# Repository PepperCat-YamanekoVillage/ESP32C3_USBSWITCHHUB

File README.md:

LICENSE -> https://creativecommons.org/licenses/by-nc-sa/4.0/

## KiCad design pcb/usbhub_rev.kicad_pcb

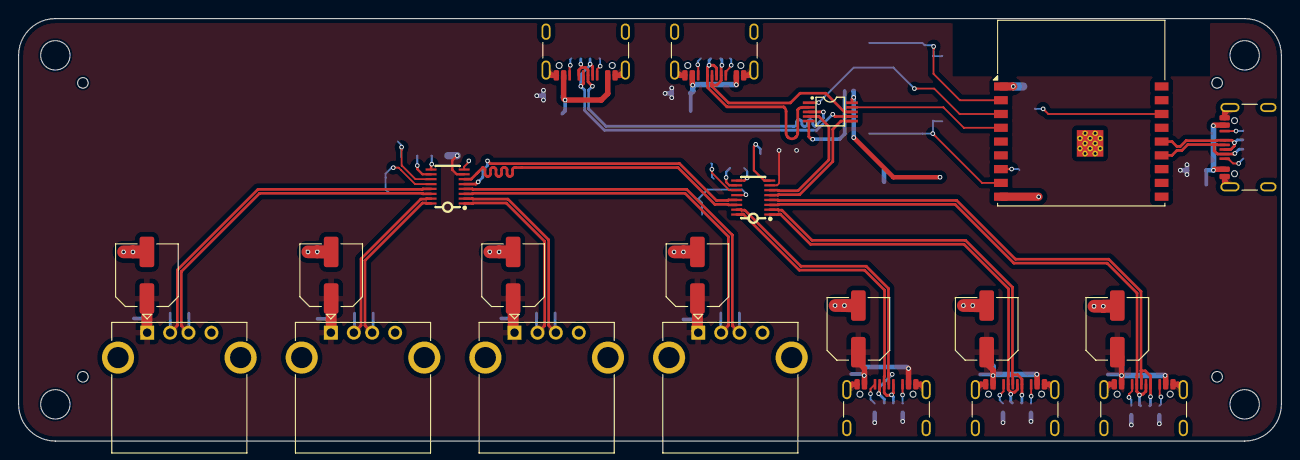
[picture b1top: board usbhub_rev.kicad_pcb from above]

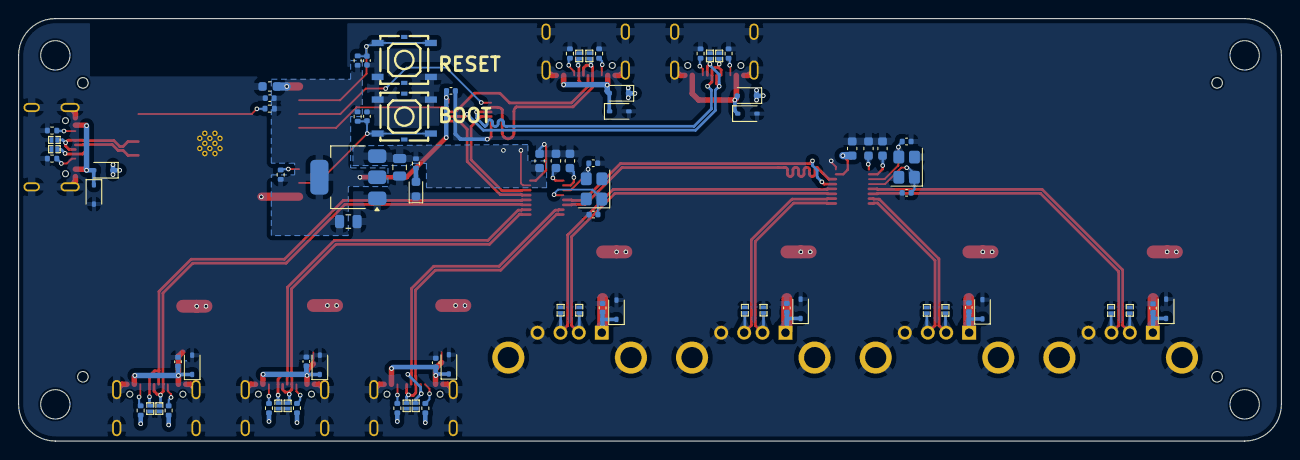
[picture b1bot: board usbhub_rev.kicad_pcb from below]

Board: 2 copper layers, 137.5 x 46.0 mm, 109 parts (80 on the bottom side), 57 nets.

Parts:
C1, C2, C7, C8, C9, C11, C12: 10uF; C_0603_1608Metric
C3, C17, C18, C20, C21, C23, C24: 100uF; C_Elec_6.3x5.4
C4, C19, C22, C25, C26, C27, C28, C29, C30, C31: 100nF; C_0402_1005Metric
C5, C6, C13, C15: 20pF; C_0402_1005Metric
C10, C14: 22uF; C_0805_2012Metric
C16: 12pF; C_0402_1005Metric
D1: LED; LED_0603_1608Metric
D2, D4, D5, D7, D8, D13, D14, D16, D17, D18, D20, D22, D23, D24, D26, D27, D29, D30, D32, D33: ESD/S3.3VmSp; DFN1006-2L_L1.0-W0.6-P0.60-BI
D3, D9, D11, D15, D19, D21, D25, D28, D31, D34: ESD/PW5V; D_SOD-323
D6, D10, D12: BAT/10V; D_SOD-323
H1, H2, H3, H4: MountingHole_3.2mm_M3_ISO7380
H5, H6, H7, H8: toolinghole
J1, J2, J3, J5, J6, J7: USB_C_Connecter; usbc_reflow
J4, J8, J9, J10: USB_A; USB_A_Kycon_KUSBX-AS1N-B_Horizontal
R1, R2, R23, R25: 10k; R_0402_1005Metric
R3, R4, R5, R6, R20, R21: 5.1k; R_0402_1005Metric
R7, R8, R9, R10, R11, R12: 56k; R_0402_1005Metric
R13: 2k; R_0402_1005Metric
SW2, SW3: SW_Push; SW-SMD_6P-L5.2-W5.2-P3.70-LS6.4
U1: ESP32-C3-WROOM-02
U2: TS3USB30EDGSR; VSSOP-10_L3.0-W3.0-P0.50-LS4.9-BL
U3, U5: SL2.1S; SSOP-16_L4.6-W2.6-P0.53-LS4.0-BL
U4: AMS1117-3.3; SOT-223-3_TabPin2
Y1, Y2: 12MHz; Crystal_SMD_3225-4Pin_3.2x2.5mm

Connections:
+3.3V: C1.2, C4.2, C14.1, C19.2, R1.1, R2.1, R23.2, R25.2, U1.1 (3V3), U2.10 (VCC), U4.2 (VO)
+5V: C2.1, C3.1, C7.1, C10.1, C17.1, C18.1, C20.1, C21.1, C23.1, C24.1, C25.2, C26.2, C27.2, C28.2, C29.2, C30.2, C31.2, D6.1 (K), D10.1 (K), D12.1 (K), D15.1 (A1), D19.1 (A1), D21.1 (A1), D25.1 (A1), D28.1 (A1), D31.1 (A1), D34.1 (A1), J4.1 (VBUS), J5.A4 (VBUS), J5.B9 (VBUS), J6.A4 (VBUS), J6.B9 (VBUS), J7.A4 (VBUS), J7.B9 (VBUS), J8.1 (VBUS), J9.1 (VBUS), J10.1 (VBUS), R7.2, R8.2, R9.2, R10.2, R11.2, R12.2, R13.1, U3.7 (VDD5), U4.3 (VI), U5.7 (VDD5)
/SELECT: U1.3 (IO4), U2.1 (S)
/deviceA1/D+: D26.2 (A2), J8.3 (D+), U5.2 (DP2)
/deviceA1/D-: D27.2 (A2), J8.2 (D-), U5.1 (DM2)
/deviceA2/D+: D29.2 (A2), J9.3 (D+), U5.16 (DP3)
/deviceA2/D-: D30.2 (A2), J9.2 (D-), U5.15 (DM3)
/deviceA3/D+: D32.2 (A2), J10.3 (D+), U5.14 (DP4)
/deviceA3/D-: D33.2 (A2), J10.2 (D-), U5.13 (DM4)
/deviceA/D+: D14.2 (A2), J4.3 (D+), U5.4 (DP1)
/deviceA/D-: D16.2 (A2), J4.2 (D-), U5.3 (DM1)
/deviceC1/D+: D17.2 (A2), J5.A6 (D+), J5.B6 (D+), U3.2 (DP2)
/deviceC1/D-: D18.2 (A2), J5.A7 (D-), J5.B7 (D-), U3.1 (DM2)
/deviceC2/D+: D22.2 (A2), J7.A6 (D+), J7.B6 (D+), U3.16 (DP3)
/deviceC2/D-: D24.2 (A2), J7.A7 (D-), J7.B7 (D-), U3.15 (DM3)
/deviceC/D+: D20.2 (A2), J6.A6 (D+), J6.B6 (D+), U3.4 (DP1)
/deviceC/D-: D23.2 (A2), J6.A7 (D-), J6.B7 (D-), U3.3 (DM1)
/esp32c3/BOOT: C16.2, R23.1, SW2.2, U1.8 (IO9)
/esp32c3/RESET: C22.2, R25.1, SW3.2, U1.2 (EN)
/esp32c3/USB_D+: D4.2 (A2), J1.A6 (D+), J1.B6 (D+), U1.14 (IO19)
/esp32c3/USB_D-: D5.2 (A2), J1.A7 (D-), J1.B7 (D-), U1.13 (IO18)
/host1/USB_D+: D8.2 (A2), J3.A6 (D+), J3.B6 (D+), U2.3 (D2+)
/host1/USB_D-: D13.2 (A2), J3.A7 (D-), J3.B7 (D-), U2.7 (D2-)
/host/USB_D+: D2.2 (A2), J2.A6 (D+), J2.B6 (D+), U2.2 (D1+)
/host/USB_D-: D7.2 (A2), J2.A7 (D-), J2.B7 (D-), U2.8 (D1-)
/hub/D+: U2.4 (D+), U3.6 (UDP)
/hub/D-: U2.6 (D-), U3.5 (UDM)
/hub/D_CHILD_D+: U3.14 (DP4), U5.6 (UDP)
/hub/D_CHILD_D-: U3.13 (DM4), U5.5 (UDM)
/~OE: U1.4 (IO5), U2.9 (~OE)
GND: C1.1, C2.2, C3.2, C4.1, C5.2, C6.1, C7.2, C8.1, C9.1, C10.2, C11.1, C12.1, C13.2, C14.2, C15.1, C16.1, C17.2, C18.2, C19.1, C20.2, C21.2, C22.1, C23.2, C24.2, C25.1, C26.1, C27.1, C28.1, C29.1, C30.1, C31.1, D1.1 (K), D2.1 (A1), D3.2 (A2), D4.1 (A1), D5.1 (A1), D7.1 (A1), D8.1 (A1), D9.2 (A2), D11.2 (A2), D13.1 (A1), D14.1 (A1), D15.2 (A2), D16.1 (A1), D17.1 (A1), D18.1 (A1), D19.2 (A2), D20.1 (A1), D21.2 (A2), D22.1 (A1), D23.1 (A1), D24.1 (A1), D25.2 (A2), D26.1 (A1), D27.1 (A1), D28.2 (A2), D29.1 (A1), D30.1 (A1), D31.2 (A2), D32.1 (A1), D33.1 (A1), D34.2 (A2), J1.A1 (GND), J1.S1 (SHIELD), J2.A1 (GND), J2.S1 (SHIELD), J3.A1 (GND), J3.S1 (SHIELD), J4.4 (GND), J4.5 (Shield), J5.A1 (GND), J5.S1 (SHIELD), J6.A1 (GND), J6.S1 (SHIELD), J7.A1 (GND), J7.S1 (SHIELD), J8.4 (GND), J8.5 (Shield), J9.4 (GND), J9.5 (Shield), J10.4 (GND), J10.5 (Shield), R3.2, R4.2, R5.2, R6.2, R20.2, R21.2, SW2.1, SW3.1, U1.9 (GND), U1.19 (GND), U2.5 (GND), U3.8 (VSS), U4.1 (GND), U5.8 (VSS), Y1.2, Y1.4, Y2.2, Y2.4
unnamed: D1.2 (A), R13.2
unnamed: D3.1 (A1), D6.2 (A), J2.A4 (VBUS), J2.B9 (VBUS)
unnamed: D9.1 (A1), D10.2 (A), J3.A4 (VBUS), J3.B9 (VBUS)
unnamed: D11.1 (A1), D12.2 (A), J1.A4 (VBUS), J1.B9 (VBUS)
unnamed: J1.A5 (CC1), R20.1
unnamed: J1.B5 (CC2), R21.1
unnamed: J2.A5 (CC1), R3.1
unnamed: J2.B5 (CC2), R4.1
unnamed: J3.A5 (CC1), R5.1
unnamed: J3.B5 (CC2), R6.1
unnamed: J5.A5 (CC1), R9.1
unnamed: J5.B5 (CC2), R10.1
unnamed: J6.A5 (CC1), R7.1
unnamed: J6.B5 (CC2), R8.1
unnamed: J7.A5 (CC1), R11.1
unnamed: J7.B5 (CC2), R12.1
unnamed: R1.2, U1.16 (IO2)
unnamed: R2.2, U1.7 (IO8)
unnamed: C8.2, U3.10 (VDD18)
unnamed: C9.2, U3.9 (VDD33)
unnamed: C5.1, U3.12 (XIN), Y1.1
unnamed: C6.2, U3.11 (XOUT), Y1.3
unnamed: C11.2, U5.10 (VDD18)
unnamed: C12.2, U5.9 (VDD33)
unnamed: C13.1, U5.12 (XIN), Y2.1
unnamed: C15.2, U5.11 (XOUT), Y2.3

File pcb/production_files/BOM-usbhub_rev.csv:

Comment,Designator,Footprint,LCSC,Quantity
TS3USB30EDGSR,U2,VSSOP-10_L3.0-W3.0-P0.50-LS4.9-BL,C131998,1
100nF,"C19,C22,C25,C26,C27,C28,C29,C30,C31,C4",C_0402_1005Metric,C1525,10
12pF,C16,C_0402_1005Metric,C1547,1
20pF,"C13,C15,C5,C6",C_0402_1005Metric,C1554,4
10uF,"C1,C11,C12,C2,C7,C8,C9",C_0603_1608Metric,C19702,7
ESD/PW5V,"D11,D15,D19,D21,D25,D28,D3,D31,D34,D9",D_SOD-323,C20615807,10
ESD/S3.3VmSp,"D13,D14,D16,D17,D18,D2,D20,D22,D23,D24,D26,D27,D29,D30,D32,D33,D4,D5,D7,D8",DFN1006-2L_L1.0-W0.6-P0.60-BI,C20617909,20
LED,D1,LED_0603_1608Metric,C2286,1
10k,"R1,R2,R23,R25",R_0402_1005Metric,C25744,4
56k,"R10,R11,R12,R7,R8,R9",R_0402_1005Metric,C25796,6
5.1k,"R20,R21,R3,R4,R5,R6",R_0402_1005Metric,C25905,6
SL2.1S,"U3,U5",SSOP-16_L4.6-W2.6-P0.53-LS4.0-BL,C2684433,2
SW_Push,"SW2,SW3",SW-SMD_6P-L5.2-W5.2-P3.70-LS6.4,C318884,2
2k,R13,R_0402_1005Metric,C4109,1
22uF,"C10,C14",C_0805_2012Metric,C45783,2
AMS1117-3.3,U4,SOT-223-3_TabPin2,C6186,1
BAT/10V,"D10,D12,D6",D_SOD-323,C7502695,3
12MHz,"Y1,Y2",Crystal_SMD_3225-4Pin_3.2x2.5mm,C9002,2
USB_A,J4,USB_A_Kycon_KUSBX-AS1N-B_Horizontal,,1
USB_C_Connecter,J5,usbc_reflow,,1
USB_C_Connecter,J6,usbc_reflow,,1
USB_C_Connecter,J7,usbc_reflow,,1
USB_A,J8,USB_A_Kycon_KUSBX-AS1N-B_Horizontal,,1
USB_A,J9,USB_A_Kycon_KUSBX-AS1N-B_Horizontal,,1
USB_A,J10,USB_A_Kycon_KUSBX-AS1N-B_Horizontal,,1
100uF,C23,C_Elec_6.3x5.4,,1
100uF,C24,C_Elec_6.3x5.4,,1
ESP32-C3-WROOM-02,U1,ESP32-C3-WROOM-02,,1
100uF,C3,C_Elec_6.3x5.4,,1
USB_C_Connecter,J3,usbc_reflow,,1
USB_C_Connecter,J1,usbc_reflow,,1
USB_C_Connecter,J2,usbc_reflow,,1
100uF,C17,C_Elec_6.3x5.4,,1
100uF,C18,C_Elec_6.3x5.4,,1
100uF,C20,C_Elec_6.3x5.4,,1
100uF,C21,C_Elec_6.3x5.4,,1
